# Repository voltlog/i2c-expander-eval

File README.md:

# i2c-expander-eval
This repository hosts the source files needed to build the I2C Expander Evaluation Board.
As shown in Voltlog #409 on Youtube.

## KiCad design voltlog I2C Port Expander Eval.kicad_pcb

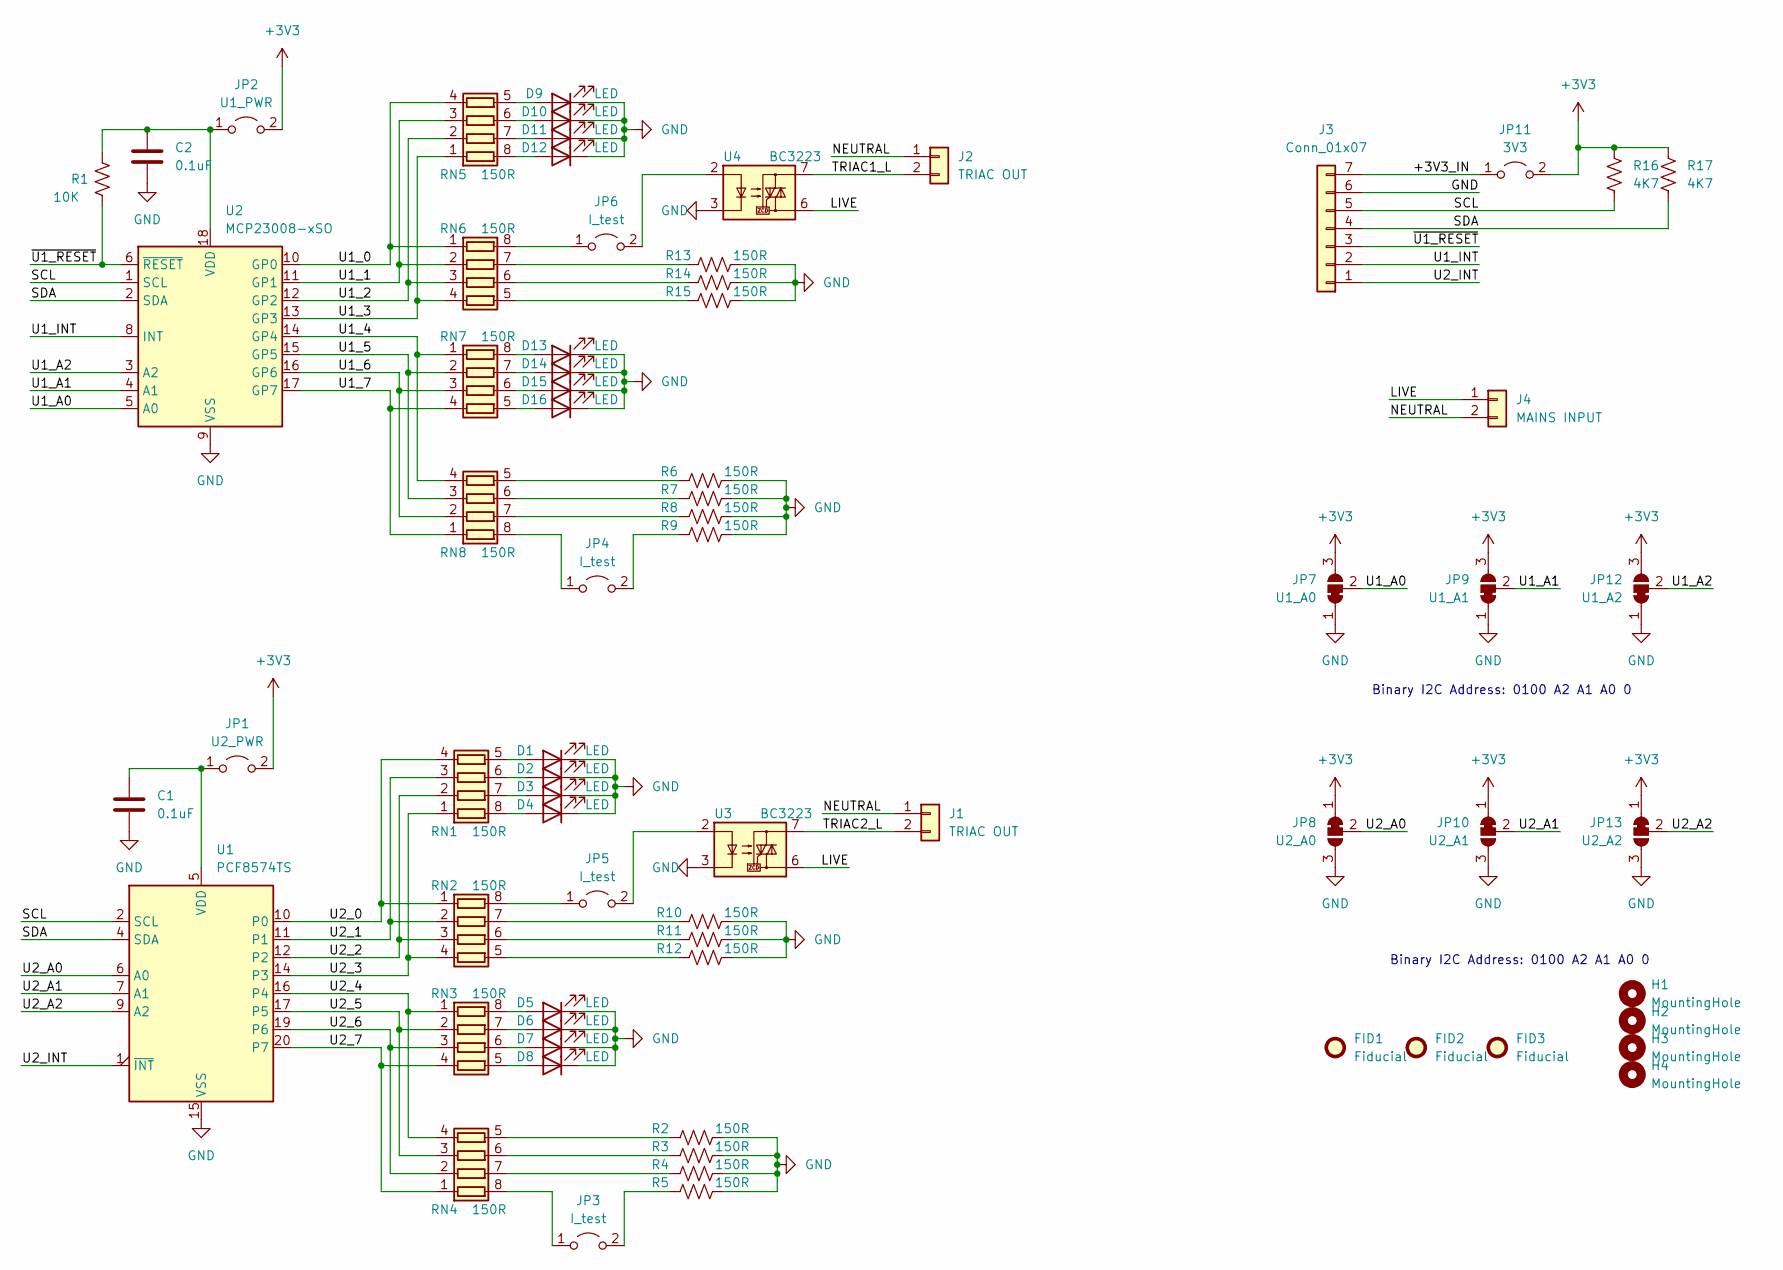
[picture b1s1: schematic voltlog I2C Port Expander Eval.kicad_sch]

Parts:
C1, C2: 0.1uF; C_0603_1608Metric
D1, D2, D3, D4, D5, D6, D7, D8, D9, D10, D11, D12, D13, D14, D15, D16: LED; LED_0603_1608Metric
FID1, FID2, FID3: Fiducial; Fiducial_0.75mm_Mask1.5mm
H1, H2, H3, H4: MountingHole; MountingHole_3.2mm_M3
J1, J2: TRIAC OUT; TerminalBlock_RND_205-00012_1x02_P5.00mm_Horizontal
J3: Conn_01x07; PinHeader_1x07_P2.54mm_Vertical
J4: MAINS INPUT; TerminalBlock_RND_205-00012_1x02_P5.00mm_Horizontal
JP1: U2_PWR; TestPoint_2Pads_Pitch2.54mm_Drill0.8mm
JP2: U1_PWR; TestPoint_2Pads_Pitch2.54mm_Drill0.8mm
JP3, JP4, JP5, JP6: I_test; TestPoint_2Pads_Pitch2.54mm_Drill0.8mm
JP7: U1_A0; SolderJumper-3_P1.3mm_Bridged12_RoundedPad1.0x1.5mm
JP8: U2_A0; SolderJumper-3_P1.3mm_Bridged12_RoundedPad1.0x1.5mm
JP9: U1_A1; SolderJumper-3_P1.3mm_Bridged12_RoundedPad1.0x1.5mm
JP10: U2_A1; SolderJumper-3_P1.3mm_Bridged12_RoundedPad1.0x1.5mm
JP11: 3V3; TestPoint_2Pads_Pitch2.54mm_Drill0.8mm
JP12: U1_A2; SolderJumper-3_P1.3mm_Bridged12_RoundedPad1.0x1.5mm
JP13: U2_A2; SolderJumper-3_P1.3mm_Bridged12_RoundedPad1.0x1.5mm
R1: 10K; R_1206_3216Metric
R2, R3, R4, R5, R6, R7, R8, R9, R10, R11, R12, R13, R14, R15: 150R; R_1206_3216Metric
R16, R17: 4K7; R_0603_1608Metric
RN1, RN2, RN3, RN4, RN5, RN6, RN7, RN8: 150R; R_Array_Convex_4x0603
U1: PCF8574TS; SSOP-20_4.4x6.5mm_P0.65mm
U2: MCP23008-xSO; SOIC-18W_7.5x11.6mm_P1.27mm
U3, U4: BC3223; SOIC-7

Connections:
+3V3: JP1.2 (B), JP2.2 (B), JP7.3 (B), JP8.1 (A), JP9.3 (B), JP10.1 (A), JP11.2 (B), JP12.3 (B), JP13.1 (A), R16.1, R17.1
/+3V3_IN: J3.7, JP11.1 (A)
/LIVE: J4.1, U3.5, U3.6, U4.5, U4.6
/NEUTRAL: J1.1, J2.1, J4.2
/SCL: J3.5, R16.2, U1.2 (SCL), U2.1 (SCL)
/SDA: J3.4, R17.2, U1.4 (SDA), U2.2 (SDA)
/TRIAC1_L: J2.2, U4.7
/TRIAC2_L: J1.2, U3.7
/U1_0: RN5.4 (R4.1), RN6.1 (R1.1), U2.10 (GP0)
/U1_1: RN5.3 (R3.1), RN6.2 (R2.1), U2.11 (GP1)
/U1_2: RN5.2 (R2.1), RN6.3 (R3.1), U2.12 (GP2)
/U1_3: RN5.1 (R1.1), RN6.4 (R4.1), U2.13 (GP3)
/U1_4: RN7.1 (R1.1), RN8.4 (R4.1), U2.14 (GP4)
/U1_5: RN7.2 (R2.1), RN8.3 (R3.1), U2.15 (GP5)
/U1_6: RN7.3 (R3.1), RN8.2 (R2.1), U2.16 (GP6)
/U1_7: RN7.4 (R4.1), RN8.1 (R1.1), U2.17 (GP7)
/U1_A0: JP7.2 (C), U2.5 (A0)
/U1_A1: JP9.2 (C), U2.4 (A1)
/U1_A2: JP12.2 (C), U2.3 (A2)
/U1_INT: J3.2, U2.8 (INT)
/U2_0: RN1.4 (R4.1), RN2.1 (R1.1), U1.10 (P0)
/U2_1: RN1.3 (R3.1), RN2.2 (R2.1), U1.11 (P1)
/U2_2: RN1.2 (R2.1), RN2.3 (R3.1), U1.12 (P2)
/U2_3: RN1.1 (R1.1), RN2.4 (R4.1), U1.14 (P3)
/U2_4: RN3.1 (R1.1), RN4.4 (R4.1), U1.16 (P4)
/U2_5: RN3.2 (R2.1), RN4.3 (R3.1), U1.17 (P5)
/U2_6: RN3.3 (R3.1), RN4.2 (R2.1), U1.19 (P6)
/U2_7: RN3.4 (R4.1), RN4.1 (R1.1), U1.20 (P7)
/U2_A0: JP8.2 (C), U1.6 (A0)
/U2_A1: JP10.2 (C), U1.7 (A1)
/U2_A2: JP13.2 (C), U1.9 (A2)
/U2_INT: J3.1, U1.1 (~INT)
/~U1_RESET: J3.3, R1.1, U2.6 (~RESET)
GND: C1.2, C2.2, D1.1 (K), D2.1 (K), D3.1 (K), D4.1 (K), D5.1 (K), D6.1 (K), D7.1 (K), D8.1 (K), D9.1 (K), D10.1 (K), D11.1 (K), D12.1 (K), D13.1 (K), D14.1 (K), D15.1 (K), D16.1 (K), J3.6, JP7.1 (A), JP8.3 (B), JP9.1 (A), JP10.3 (B), JP12.1 (A), JP13.3 (B), R2.2, R3.2, R4.2, R5.2, R6.2, R7.2, R8.2, R9.2, R10.2, R11.2, R12.2, R13.2, R14.2, R15.2, U1.15 (VSS), U2.9 (VSS), U3.1, U3.3, U3.4, U4.1, U4.3, U4.4
unnamed: C1.1, JP1.1 (A), U1.5 (VDD)
unnamed: C2.1, JP2.1 (A), R1.2, U2.18 (VDD)
unnamed: D1.2 (A), RN1.5 (R4.2)
unnamed: D2.2 (A), RN1.6 (R3.2)
unnamed: D3.2 (A), RN1.7 (R2.2)
unnamed: D4.2 (A), RN1.8 (R1.2)
unnamed: D5.2 (A), RN3.8 (R1.2)
unnamed: D6.2 (A), RN3.7 (R2.2)
unnamed: D7.2 (A), RN3.6 (R3.2)
unnamed: D8.2 (A), RN3.5 (R4.2)
unnamed: D9.2 (A), RN5.5 (R4.2)
unnamed: D10.2 (A), RN5.6 (R3.2)
unnamed: D11.2 (A), RN5.7 (R2.2)
unnamed: D12.2 (A), RN5.8 (R1.2)
unnamed: D13.2 (A), RN7.8 (R1.2)
unnamed: D14.2 (A), RN7.7 (R2.2)
unnamed: D15.2 (A), RN7.6 (R3.2)
unnamed: D16.2 (A), RN7.5 (R4.2)
unnamed: JP3.1 (A), RN4.8 (R1.2)
unnamed: JP3.2 (B), R5.1
unnamed: JP4.1 (A), RN8.8 (R1.2)
unnamed: JP4.2 (B), R9.1
unnamed: JP5.1 (A), RN2.8 (R1.2)
unnamed: JP5.2 (B), U3.2
unnamed: JP6.1 (A), RN6.8 (R1.2)
unnamed: JP6.2 (B), U4.2
unnamed: R2.1, RN4.5 (R4.2)
unnamed: R3.1, RN4.6 (R3.2)
unnamed: R4.1, RN4.7 (R2.2)
unnamed: R6.1, RN8.5 (R4.2)
unnamed: R7.1, RN8.6 (R3.2)
unnamed: R8.1, RN8.7 (R2.2)
unnamed: R10.1, RN2.7 (R2.2)
unnamed: R11.1, RN2.6 (R3.2)
unnamed: R12.1, RN2.5 (R4.2)
unnamed: R13.1, RN6.7 (R2.2)
unnamed: R14.1, RN6.6 (R3.2)
unnamed: R15.1, RN6.5 (R4.2)

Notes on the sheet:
Binary I2C Address: 0100 A2 A1 A0 0

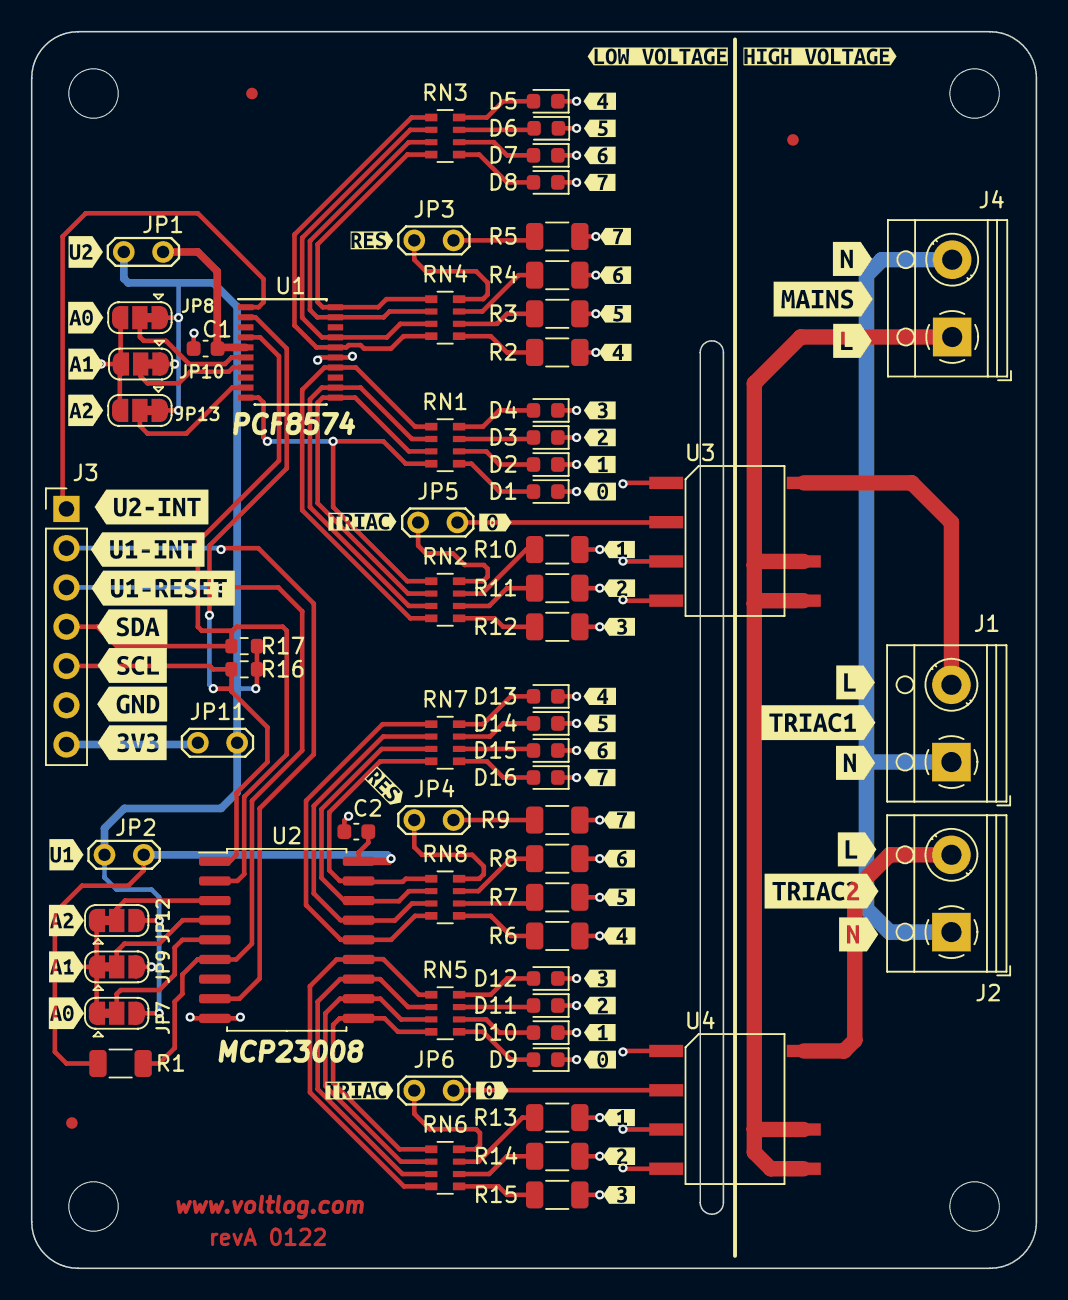
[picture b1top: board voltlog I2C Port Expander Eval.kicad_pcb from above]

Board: 2 copper layers, 65.0 x 80.0 mm, 133 parts (0 on the bottom side), 72 nets.

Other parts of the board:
kibuzzard-61D6A8A9: G***; kibuzzard-61D6A8A9
kibuzzard-61D6A9B1: G***; kibuzzard-61D6A9B1
kibuzzard-61D6A96C: G***; kibuzzard-61D6A96C
kibuzzard-61D6A99E: G***; kibuzzard-61D6A99E
kibuzzard-61D6A939: G***; kibuzzard-61D6A939
kibuzzard-61D6A941: G***; kibuzzard-61D6A941
kibuzzard-61D6A986: G***; kibuzzard-61D6A986
kibuzzard-61D6A996: G***; kibuzzard-61D6A996
kibuzzard-61D6AA1A: G***; kibuzzard-61D6AA1A
kibuzzard-61D6AA3A: G***; kibuzzard-61D6AA3A
kibuzzard-61D6AA27: G***; kibuzzard-61D6AA27
kibuzzard-61D6AA30: G***; kibuzzard-61D6AA30
kibuzzard-61D6AAA3: G***; kibuzzard-61D6AAA3
kibuzzard-61D6AAB0: G***; kibuzzard-61D6AAB0
kibuzzard-61D6AAC0: G***; kibuzzard-61D6AAC0
kibuzzard-61D6B2E5: G***; kibuzzard-61D6B2E5
kibuzzard-61D6B2FB: G***; kibuzzard-61D6B2FB
kibuzzard-61D6B5B0: G***; kibuzzard-61D6B5B0
kibuzzard-61D6B07C, kibuzzard-61D6B07C#2, kibuzzard-61D6B07C#3, kibuzzard-61D6B07C#4: G***; kibuzzard-61D6B07C
kibuzzard-61D6B08B, kibuzzard-61D6B08B#2, kibuzzard-61D6B08B#3, kibuzzard-61D6B08B#4: G***; kibuzzard-61D6B08B
kibuzzard-61D6B014, kibuzzard-61D6B014#2, kibuzzard-61D6B014#3, kibuzzard-61D6B014#4: G***; kibuzzard-61D6B014
kibuzzard-61D6B024, kibuzzard-61D6B024#2, kibuzzard-61D6B024#3, kibuzzard-61D6B024#4: G***; kibuzzard-61D6B024
kibuzzard-61D6B031, kibuzzard-61D6B031#2, kibuzzard-61D6B031#3, kibuzzard-61D6B031#4: G***; kibuzzard-61D6B031
kibuzzard-61D6B039, kibuzzard-61D6B039#2, kibuzzard-61D6B039#3, kibuzzard-61D6B039#4: G***; kibuzzard-61D6B039
kibuzzard-61D6B52E, kibuzzard-61D6B52E#2, kibuzzard-61D6B52E#3: G***; kibuzzard-61D6B52E
kibuzzard-61D6B53A, kibuzzard-61D6B53A#2, kibuzzard-61D6B53A#3: G***; kibuzzard-61D6B53A
kibuzzard-61D6B083, kibuzzard-61D6B083#2, kibuzzard-61D6B083#3, kibuzzard-61D6B083#4: G***; kibuzzard-61D6B083
kibuzzard-61D6B091, kibuzzard-61D6B091#2, kibuzzard-61D6B091#3, kibuzzard-61D6B091#4: G***; kibuzzard-61D6B091
kibuzzard-61D6B574: G***; kibuzzard-61D6B574
kibuzzard-61D6B590: G***; kibuzzard-61D6B590
kibuzzard-61D6B616, kibuzzard-61D6B616#2: G***; kibuzzard-61D6B616
kibuzzard-61D6B629, kibuzzard-61D6B629#2: G***; kibuzzard-61D6B629
